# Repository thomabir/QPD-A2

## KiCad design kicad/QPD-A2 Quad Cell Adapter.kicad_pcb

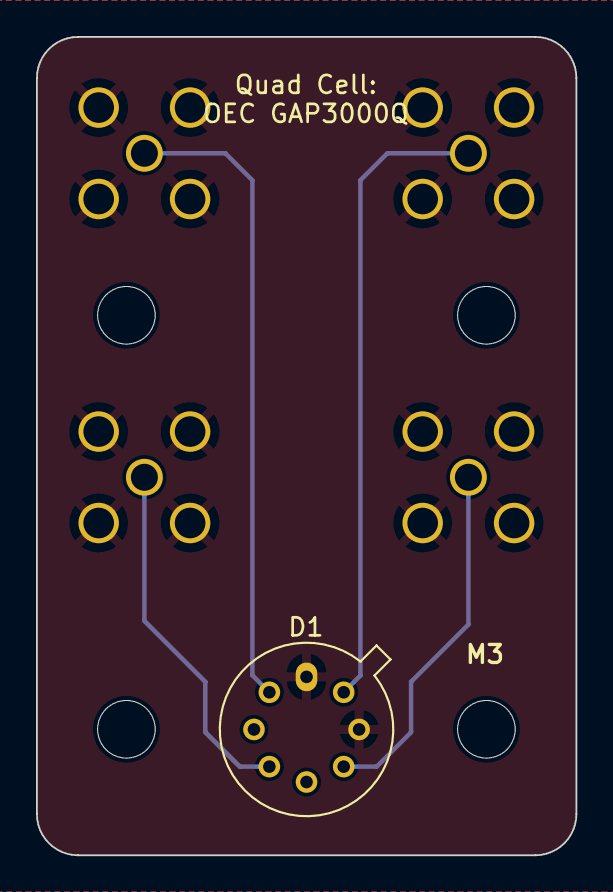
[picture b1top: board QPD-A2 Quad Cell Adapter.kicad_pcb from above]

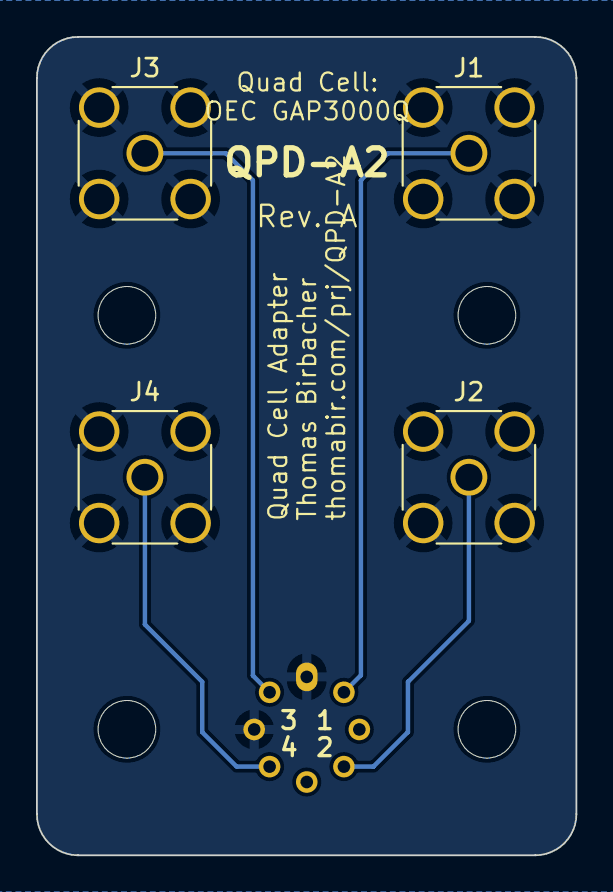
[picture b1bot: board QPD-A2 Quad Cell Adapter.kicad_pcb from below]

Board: 2 copper layers, 30.0 x 45.5 mm, 9 parts (4 on the bottom side), 5 nets.

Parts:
D1: quadrant_photodiode; TO-5-8 OEC GAPQ3000
H1, H2, H3, H4: MountingHole; MountingHole_3.2mm_M3_DIN965
J1, J2, J3, J4: SMA; SMA_Amphenol_132134_Vertical

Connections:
GND: D1.2 (Case_GND), D1.8 (Cathode), J1.2, J2.2, J3.2, J4.2
unnamed: D1.3 (Anode_A), J1.1
unnamed: D1.5 (Anode_B), J2.1
unnamed: D1.1 (Anode_C), J3.1
unnamed: D1.7 (Anode_D), J4.1
